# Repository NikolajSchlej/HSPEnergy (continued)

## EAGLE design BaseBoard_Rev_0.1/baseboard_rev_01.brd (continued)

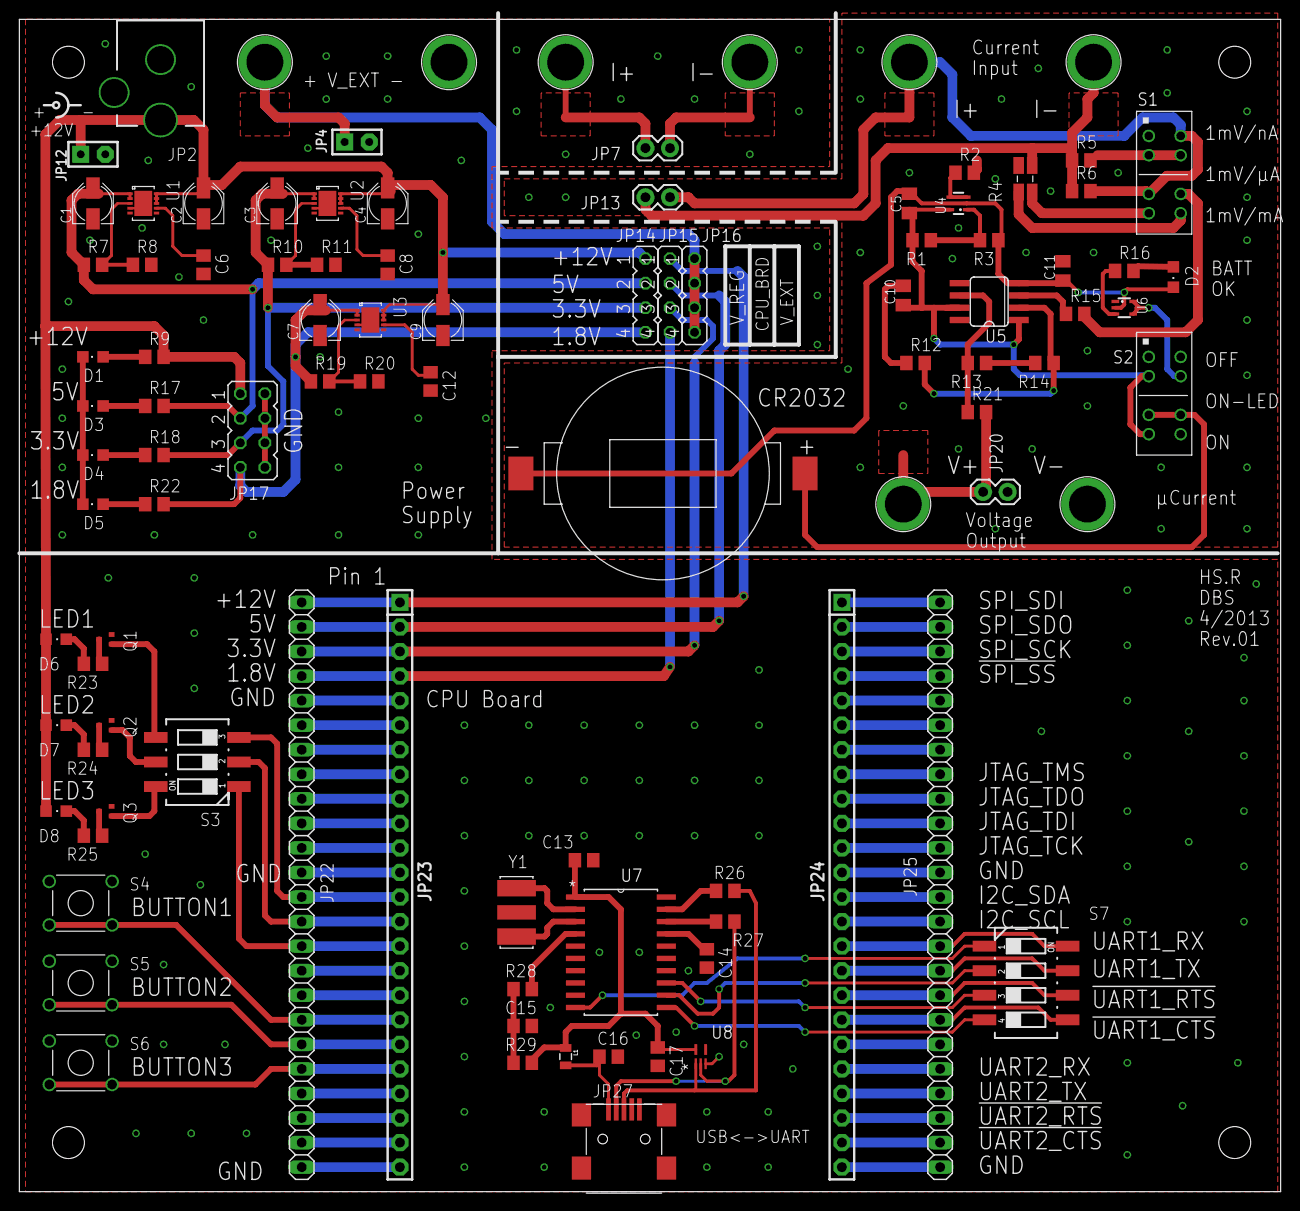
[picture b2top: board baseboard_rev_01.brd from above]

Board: 2 copper layers, 130.5 x 121.3 mm, 102 parts (0 on the bottom side), 105 nets.

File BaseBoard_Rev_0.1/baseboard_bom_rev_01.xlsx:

Designator | Quantity | Designator | Value1 | Value2 | Value3 | Package | Description | Manufacturer | Manufacturer # | Farnell # | Digikey # | Unit price € | Total Price €
Baseboard |  |  |  |  |  |  |  |  |  |  |  |  | 36.798999999999999
 | 3 | U1,U2,U3 | - |  |  | DFN10 | LDO voltage regulator |  | NCP3337MNADJR2G | 1901652 |  | 1.39 | 4.17
 | 6 | C1,C2,C3,C4,C7,C9 | 1uF |  |  | PANASONIC_B | Capacitor, polarized |  | EEE1HA010SR | 9697063 |  | 0.19900000000000001 | 1.194
 | 7 | C5,C10,C11,C13, C14, C15, C17 | 100nF |  |  | 0805 | Capacitor | Multicomp |  | 1759265 |  | 1.0999999999999999E-2 | 7.6999999999999999E-2
 | 4 | C6, C8, C12, C16 | 10nF |  |  | 0805 | Capacitor | Kemet |  | 1414662 |  | 2.1000000000000001E-2 | 8.4000000000000005E-2
 | 1 | JP2 | 1.95mm |  |  | - | DC connector | Multicomp |  | 1737246 |  | 0.64900000000000002 | 0.64900000000000002
 | 5 | R1,R3,R8,R11,R20 | 100k | 0.01 |  | 0805 | Resistor | WELWYN |  | 1099816 |  | 5.8000000000000003E-2 | 0.29000000000000004
 | 1 | S3 | 219-03 |  |  | - | DIP switch |  | MCEMR-03-T | 1524006 |  | 0.86699999999999999 | 0.86699999999999999
 | 1 | S7 | 219-04 |  |  | - | DIP switch |  | MCEMR-04-T | 1524007 |  | 0.94199999999999995 | 0.94199999999999995
 | 1 | L1 | 40 Ohm | 4A |  | 0805 | Inductor |  |  | 2292459 |  | 4.2999999999999997E-2 | 4.2999999999999997E-2
 | 3 | Q1, Q2, Q3 | PDTC114E |  |  | SOT416 | SMT resistor-equipped transistor | NXP | PDTC114EE | 1757984 | - | 1.7999999999999999E-2 | 5.3999999999999992E-2
 | 1 | R10 | 165k | 0.01 |  | 0805 | Resistor | Vishay |  | 2139046 |  | 8.0000000000000002E-3 | 8.0000000000000002E-3
 | 2 | R16, R28 | 470R | 0.01 |  | 0805 | Resistor |  |  | 1099798 |  | 1.4999999999999999E-2 | 0.03
 | 1 | R19 | 44k | 0.01 |  | 0805 | Resistor |  |  | 2141459 |  | 2.5999999999999999E-2 | 2.5999999999999999E-2
 | 3 | R2, R15, R21 | 100R | 0.01 |  | 0805 | Resistor |  |  | 1887253 |  | 6.2E-2 | 0.186
 | 2 | R26, R27 | 27R | 0.01 |  | 0805 | Resistor |  |  | 1500696 |  | 4.8000000000000001E-2 | 9.6000000000000002E-2
 | 1 | R29 | 10k | 0.01 |  | 0805 | Resistor |  |  | 1612522 |  | 3.2000000000000001E-2 | 3.2000000000000001E-2
 | 1 | R5 | 10R | 0.1% |  | 0805 | Resistor |  |  | 2008313 |  | 0.189 | 0.189
 | 1 | R6 | 10K | 0.1% |  | 0805 | Resistor |  |  | 1653282 |  | 0.10199999999999999 | 0.10199999999999999
 | 1 | R12 | 1K | 0.1% |  | 0805 | Resistor |  |  | 1653252 |  | 0.10199999999999999 | 0.10199999999999999
 | 1 | R13 | 24K | 0.1% |  | 0805 | Resistor |  |  | 1506115 |  | 0.20399999999999999 | 0.20399999999999999
 | 1 | R14 | 75K | 0.1% |  | 0805 | Resistor |  |  | 1653312 |  | 0.10199999999999999 | 0.10199999999999999
 | 1 | R7 | 300k | 0.01 |  | 0805 | Resistor |  |  | 1400387 |  | 2.3E-2 | 2.3E-2
 | 4 | R9,R23, R24, R25 | 5k6 | 0.01 |  | 0805 | Resistor, LED, 12V |  |  | 1500725 |  | 4.2000000000000003E-2 | 0.16800000000000001
 | 1 | R17 | 2k2 | 0.01 |  | 0805 | Resistor, LED, 5V |  |  | 1500692 |  | 0.252 | 0.252
 | 1 | R18 | 820R | 0.01 |  | 0805 | Resistor, LED, 3.3V |  |  | 1100314 |  | 2.1999999999999999E-2 | 2.1999999999999999E-2
 | 1 | R22 | 56R | 0.01 |  | 0805 | Resistor, LED, 1.8V |  |  | 1500723 |  | 7.8E-2 | 7.8E-2
 | 3 | S4, S5, S6 | - |  |  | - | Switch SPST-NO | ALPS | SKHHBWA010 | 2056816 |  | 0.16200000000000001 | 0.64800000000000002
 | 4 | D1, D3, D4, D5 | 1.8V | 2mA |  | 0805 | LED red | ROHM |  | 1685056 |  | 0.626 | 2.504
 | 4 | D2, D6, D7, D8 | 1.8V | 2mA |  | 0805 | LED orange | ROHM |  | 1685055 |  | 0.626 | 2.504
 | 2 | JP22, JP25 | 1x24 |  |  | - | pin header male |  |  | 1593425 |  | 0.67100000000000004 | 1.3420000000000001
 | 2 | JP23, JP24 | 1x24 |  |  | - | pin header female |  |  | 1593472 |  | 0.91800000000000004 | 1.8360000000000001
 | 5 | JP4, JP12,JP7, JP13, JP20 | 1x02 |  |  | - | pin header male |  |  | 1022245 |  | 0.113 | 0.56500000000000006
 | 1 | JP17 | 2x04 |  |  | - | pin header male |  |  | 1022233 |  | 0.47699999999999998 | 0.47699999999999998
 | 3 | JP14, JP15, JP16 | 1x04 |  |  | - | pin header male |  |  | 1022251 |  | 0.22900000000000001 | 0.68700000000000006
 | 4 | JP3, JP6, JP9, JP19 | - |  |  | - | 4mm Banana conector, red |  |  | 1698950 |  | 0.874 | 3.496
 | 4 | JP5,JP8,JP10,JP21 | - |  |  | - | 4mm Banana conector, black |  |  | 1698951 |  | 0.874 | 3.496
uCurrent
 | 1 | U4 |  |  |  | SC70-5L | uCurrent: op amp |  | LMV321IDCKR | 1651880 |  | 0.317 | 0.317
 | 1 | U6 |  |  |  | DCK | uCurrent: voltage supervisor | Texas Instruments | TPS3801L30DCKR | 2075439 |  | 1.03 | 1.03
 | 1 | U5 |  |  |  | 8 SO | uCurrent: op amp | Maxim | MAX4239ASA+ | - | MAX4239ASA+-ND | 2.02 | 2.02
 | 1 | R4 | 0R01 | 5.0000000000000001E-3 |  | 1206 | KELVIN R01 | Ohmite | LVK12R010DER | 1462291 |  | 0.58099999999999996 | 0.58099999999999996
 | 2 | S1,S2 | DP3T |  |  | custom | slide switch | C&K Components | JS203011CQN | - | 401-2004-ND | 0.46 | 0.92
 | 1 | JP18 |  |  |  | custom | CR2032 Battery holder | Renata | SMTU 2032-LF | 1216354 |  | 0.85499999999999998 | 0.85499999999999998
 | 1 |  |  |  |  | - | CR2032 Battery
USB-to-serial
 | 1 | U8 |  |  |  | SOT-5 | USB ESD protection array | Texas Instruments | TPD3E001DRLR | 1603422 |  | 0.21 | 0.21
 | 1 | U7 |  |  |  | SOIC | USB-to-serial converter | Microchip | MCP2200-I/SO | 1781148 |  | 1.81 | 1.81
 | 1 | Y1 |  |  | 12MHz | custom | Quarz oscillator |  | PBRC12.00HR50X0RZ | 1218535 |  | 0.75900000000000001 | 0.75900000000000001
 | 1 | JP27 | - | - | - |  | mini USB B, female |  | 10033526-N3212MLF | 2112367 |  | 0.752 | 0.752

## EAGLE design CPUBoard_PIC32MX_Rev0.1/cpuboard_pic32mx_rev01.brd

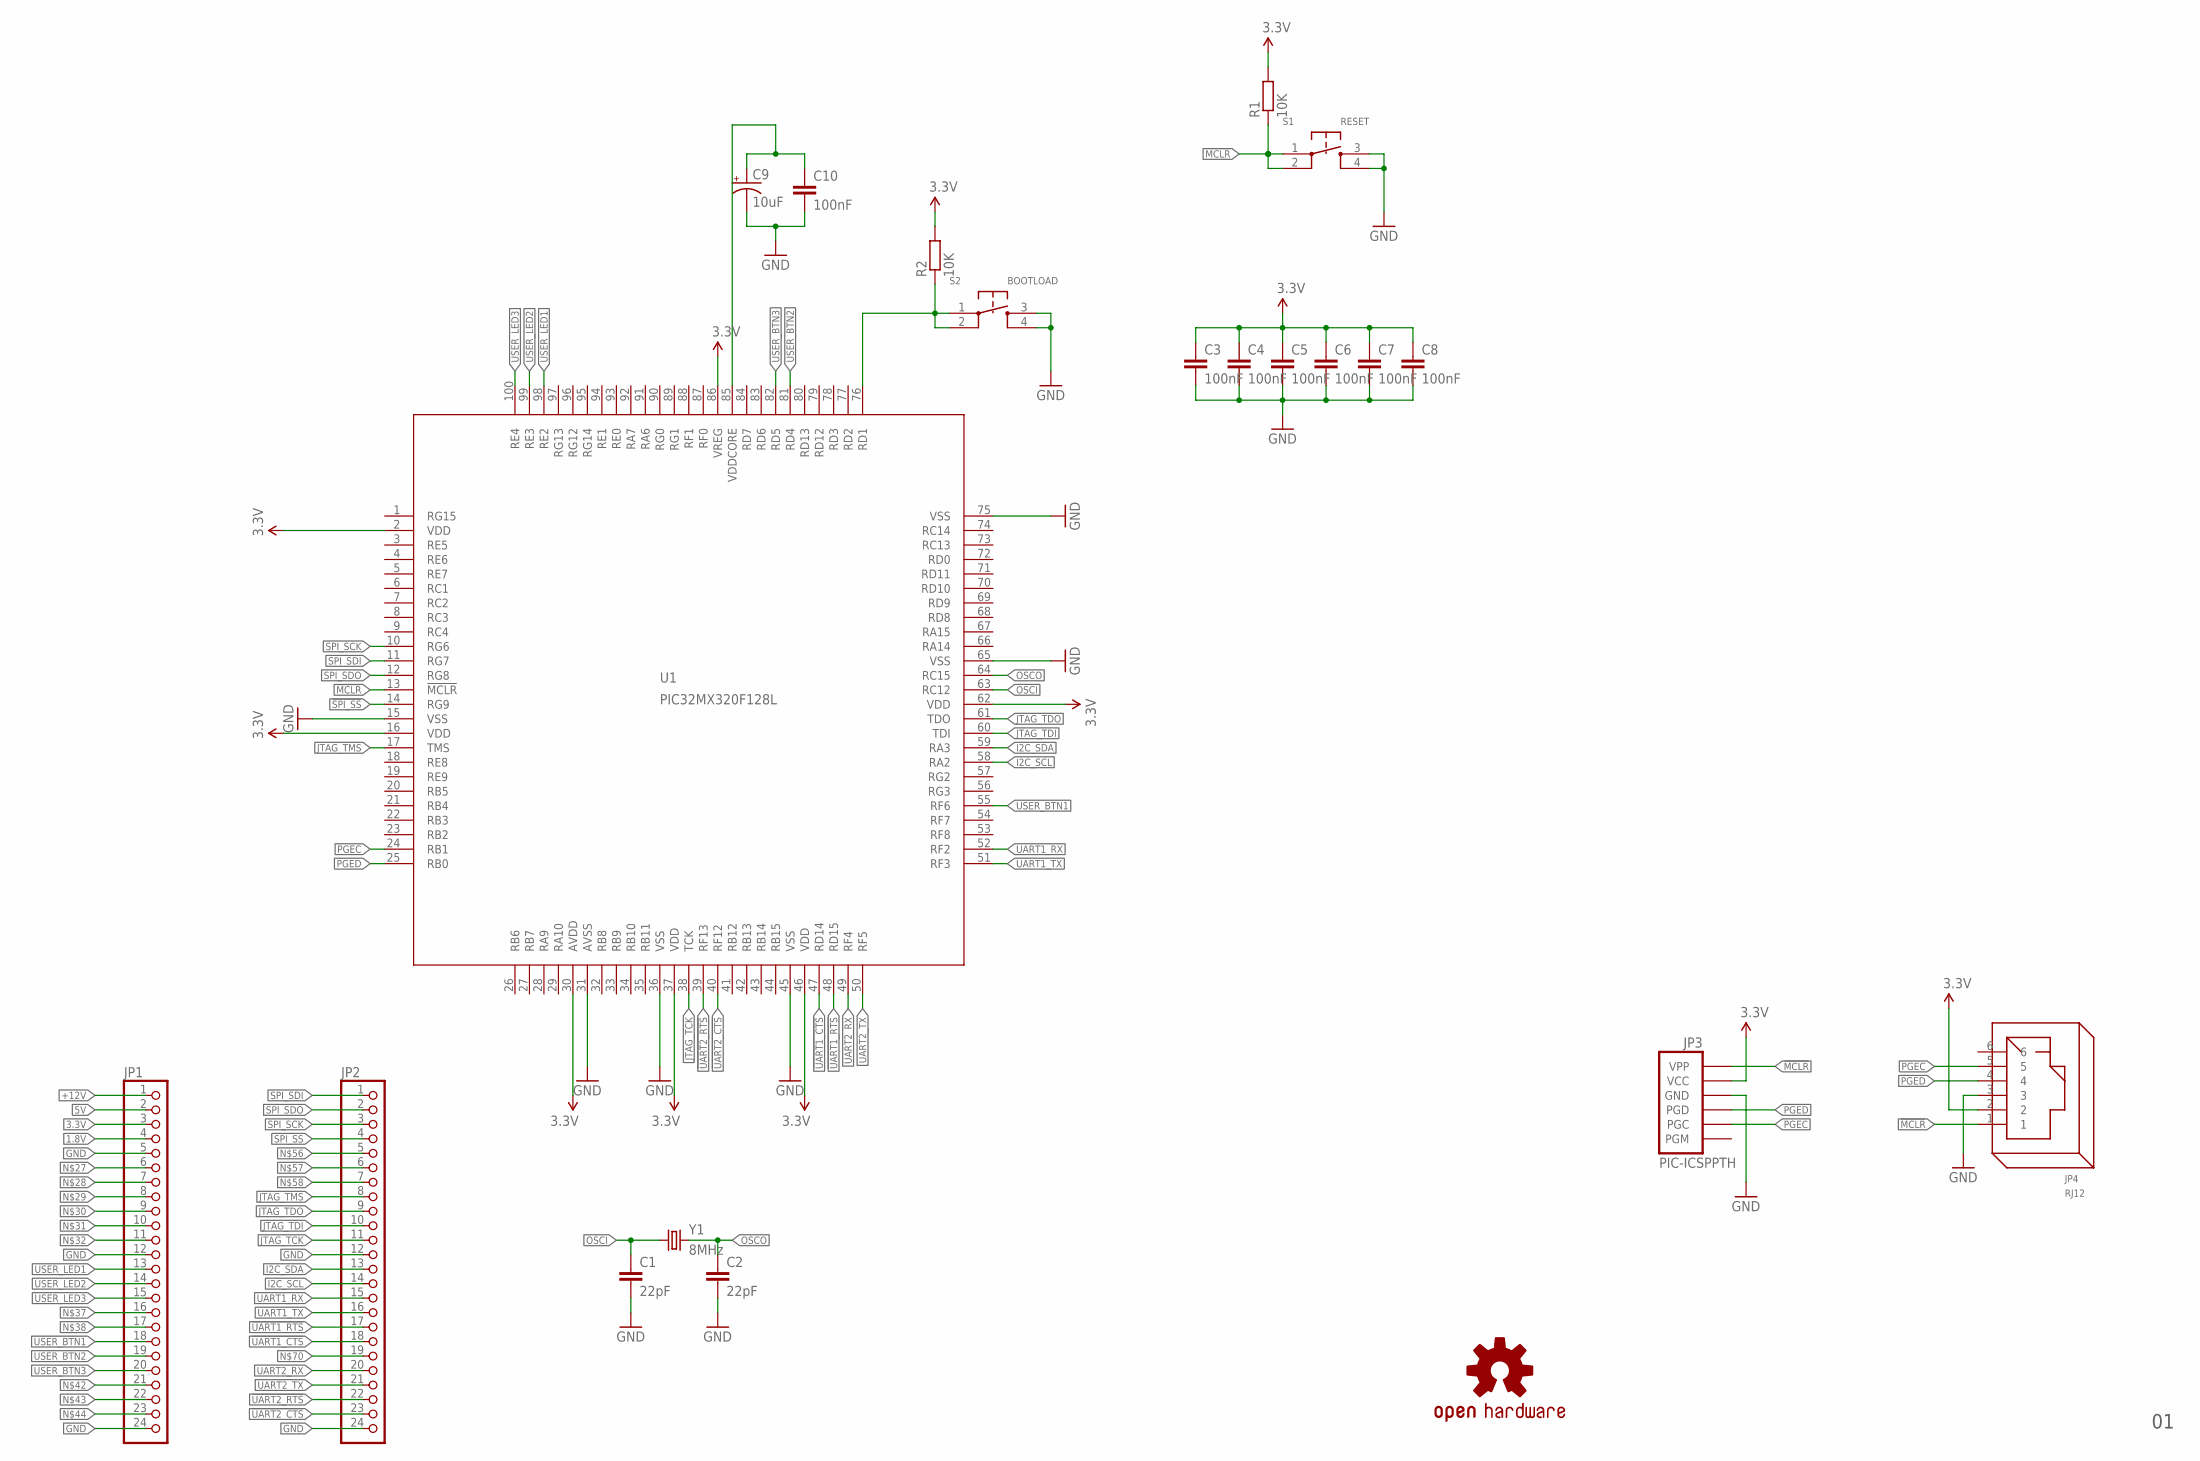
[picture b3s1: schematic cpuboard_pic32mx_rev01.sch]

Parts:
C1, C2: 22pF; C0805K
C3, C4, C5, C6, C7, C8, C10: 100nF; C0805K
C9: 10uF; PANASONIC_D
JP1, JP2: PINHD-1X24; 1X24
JP3: PIC-ICSPPTH; MOLEX-1X6
JP4: RJ12
R1, R2: 10K; R0805
S1: RESET; SWITCH_TROUGHHOLE
S2: BOOTLOAD; SWITCH_TROUGHHOLE
U1: PIC32MX320F128L; SQFP-S-12X12-100
U$1: OSHW-LOGOS; OSHW-LOGO-S
Y1: 8MHz; HC49UP

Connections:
1.8V: JP1.4
3.3V: C3.1, C4.1, C5.1, C6.1, C7.1, C8.1, JP1.3, JP3.5 (VCC), JP4.2, R1.2, R2.2, U1.2 (VDD), U1.16 (VDD), U1.30 (AVDD), U1.37 (VDD), U1.46 (VDD), U1.62 (VDD), U1.86 (VREG)
5V: JP1.2
!MCLR: JP3.6 (VPP), JP4.1, R1.1, S1.1, S1.2, U1.13 (!MCLR)
!SPI_SS: JP2.4, U1.14 (RG9)
!UART1_CTS: JP2.18, U1.47 (RD14)
!UART1_RTS: JP2.17, U1.48 (RD15)
!UART2_CTS: JP2.23, U1.40 (RF12)
!UART2_RTS: JP2.22, U1.39 (RF13)
+12V: JP1.1
GND: C1.2, C2.2, C3.2, C4.2, C5.2, C6.2, C7.2, C8.2, C9.-, C10.2, JP1.5, JP1.12, JP1.24, JP2.12, JP2.24, JP3.4 (GND), JP4.3, S1.3, S1.4, S2.3, S2.4, U1.15 (VSS), U1.31 (AVSS), U1.36 (VSS), U1.45 (VSS), U1.65 (VSS), U1.75 (VSS)
I2C_SCL: JP2.14, U1.58 (RA2)
I2C_SDA: JP2.13, U1.59 (RA3)
JTAG_TCK: JP2.11, U1.38 (TCK)
JTAG_TDI: JP2.10, U1.60 (TDI)
JTAG_TDO: JP2.9, U1.61 (TDO)
JTAG_TMS: JP2.8, U1.17 (TMS)
unnamed: C9.+, C10.1, U1.85 (VDDCORE)
unnamed: R2.1, S2.1, S2.2, U1.76 (RD1)
OSCI: C1.1, U1.63 (RC12), Y1.1
OSCO: C2.1, U1.64 (RC15), Y1.2
PGEC: JP3.2 (PGC), JP4.5, U1.24 (RB1)
PGED: JP3.3 (PGD), JP4.4, U1.25 (RB0)
SPI_SCK: JP2.3, U1.10 (RG6)
SPI_SDI: JP2.1, U1.11 (RG7)
SPI_SDO: JP2.2, U1.12 (RG8)
UART1_RX: JP2.15, U1.52 (RF2)
UART1_TX: JP2.16, U1.51 (RF3)
UART2_RX: JP2.20, U1.49 (RF4)
UART2_TX: JP2.21, U1.50 (RF5)
USER_BTN1: JP1.18, U1.55 (RF6)
USER_BTN2: JP1.19, U1.81 (RD4)
USER_BTN3: JP1.20, U1.82 (RD5)
USER_LED1: JP1.13, U1.98 (RE2)
USER_LED2: JP1.14, U1.99 (RE3)
USER_LED3: JP1.15, U1.100 (RE4)

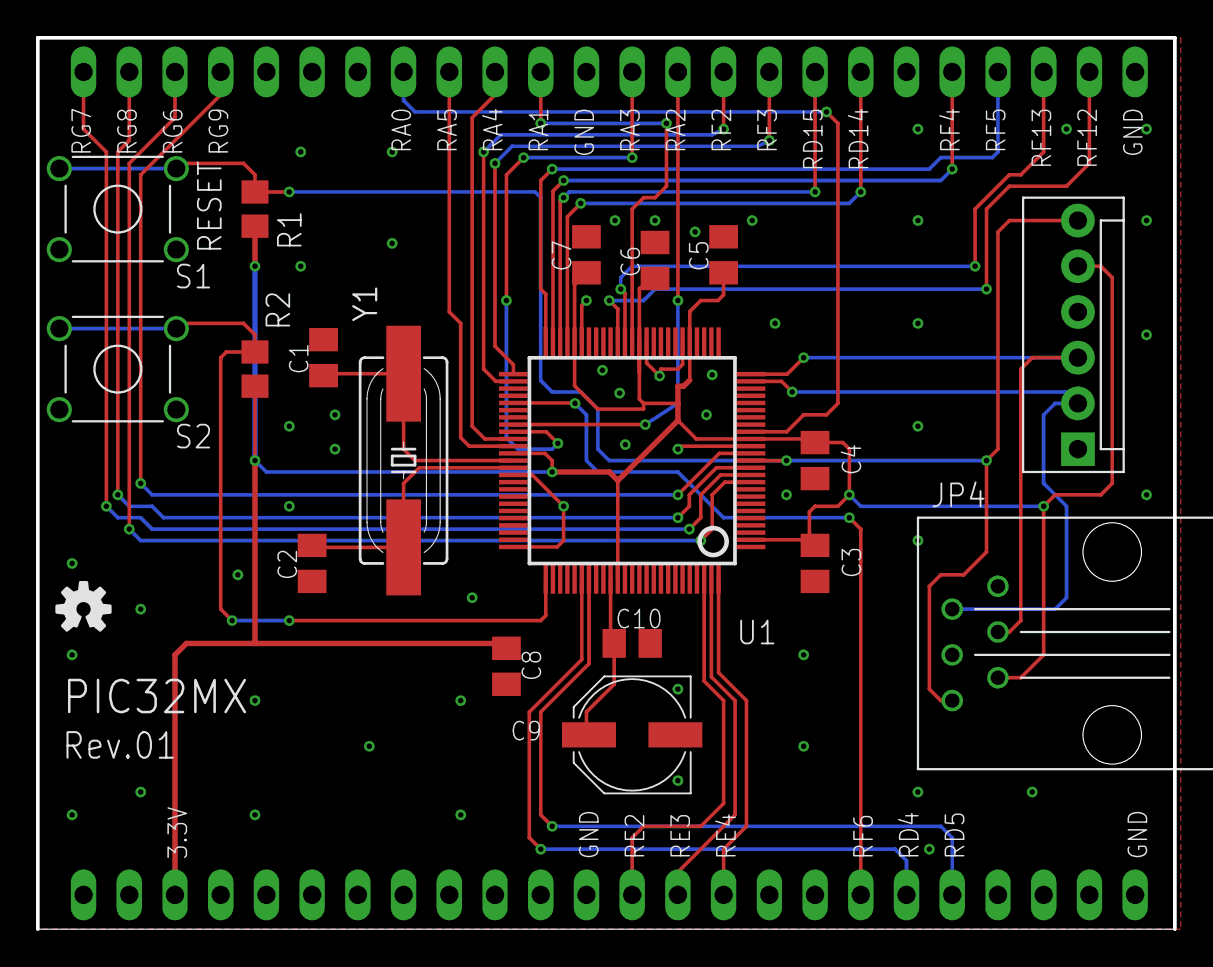
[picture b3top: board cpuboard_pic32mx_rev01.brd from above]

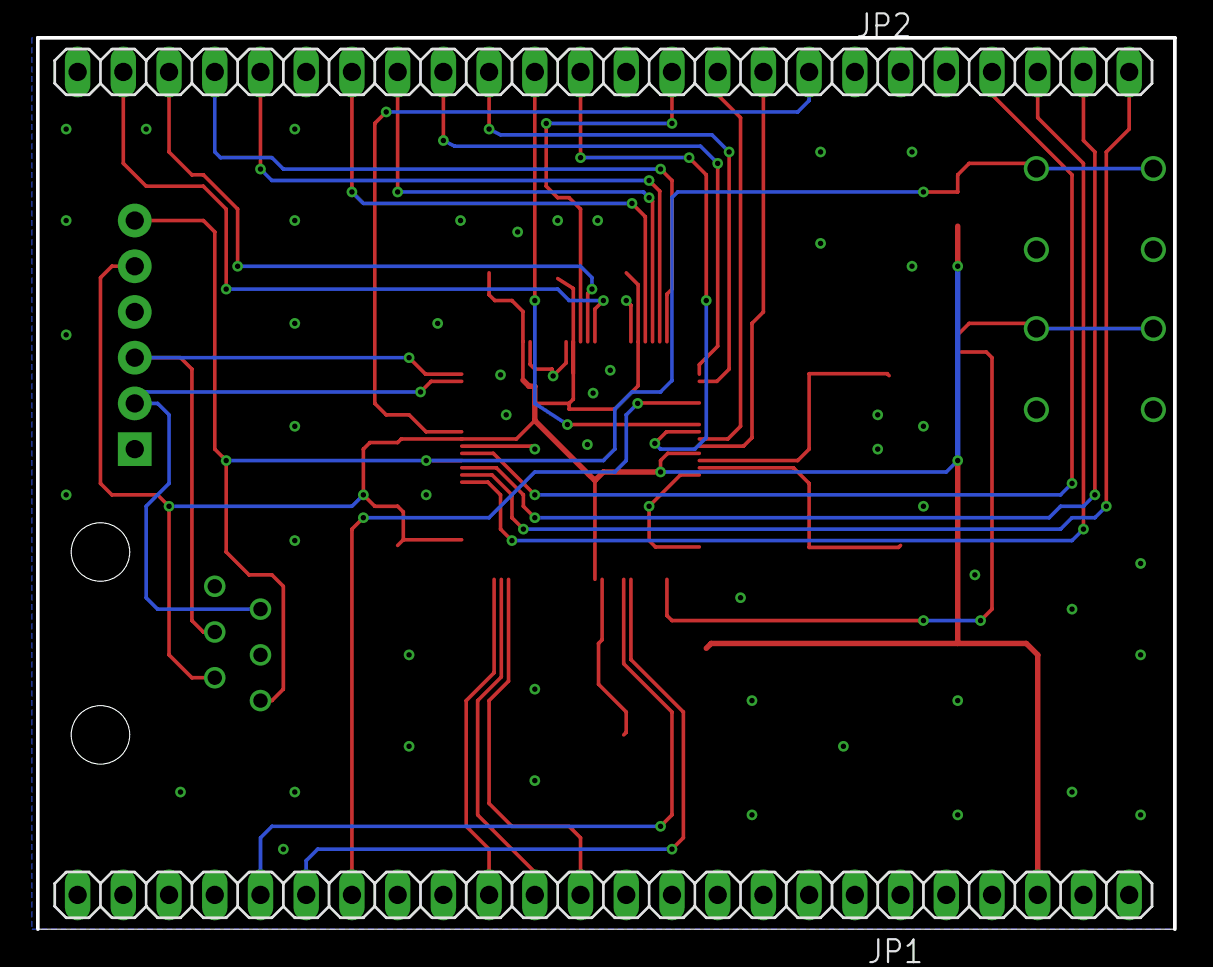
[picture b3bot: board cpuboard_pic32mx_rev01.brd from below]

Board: 2 copper layers, 63.2 x 49.5 mm, 21 parts (2 on the bottom side), 33 nets.

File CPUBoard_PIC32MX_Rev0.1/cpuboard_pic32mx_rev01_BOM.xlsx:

Designator | Quantity | Designator | Value1 | Value2 | Value3 | Package | Description | Manufacturer | Manufacturer # | Farnell # | Digikey # | Unit price € | Total Price €
 | 1 |  |  |  |  | TQFP-100 | Microcontroller | Microchip | PIC32MX320F128L | 1523321 | PIC32MX320F128L-80I/PT | 6.67 | 6.67
 | 1 | C9 | 10uF | 50V | +/- 20% | SMT | Aluminum Electrolytic Capacitor | Panasonic | EEEFK1H100P | 1850117 |  | 0.26900000000000002 | 0.26900000000000002
 | 2 |  | 1x24 |  |  |  | pin header male |  |  | 1593425 |  | 0.67100000000000004 | 1.3420000000000001
 | 2 | C1,C2 | 22pF |  |  | 0805 | Capacitor |  |  | 1885437 |  | 0.29699999999999999 | 0.59399999999999997
 | 7 | C3,C4,C5,C6,C7,C8,C10 | 100nF |  |  | 0805 | Capacitor | Multicomp |  | 1759265 |  | 1.0999999999999999E-2 | 7.6999999999999999E-2
DNP | 1 | JP3 |  |  |  |  | Programming connector
 | 1 | JP4 | RJ12 |  |  |  | Programming connector |  |  | 3938359 |  | 1.18 | 1.18
 | 2 | R1,R2 | 10K | 1% |  | 0805 | Resistor |  |  | 1612522 |  | 3.2000000000000001E-2 | 6.4000000000000001E-2
 | 2 | S1,S2 |  |  |  |  | tactile switch | ALPS | SKHHBWA010 | 2056816 |  | 0.16200000000000001 | 0.16200000000000001

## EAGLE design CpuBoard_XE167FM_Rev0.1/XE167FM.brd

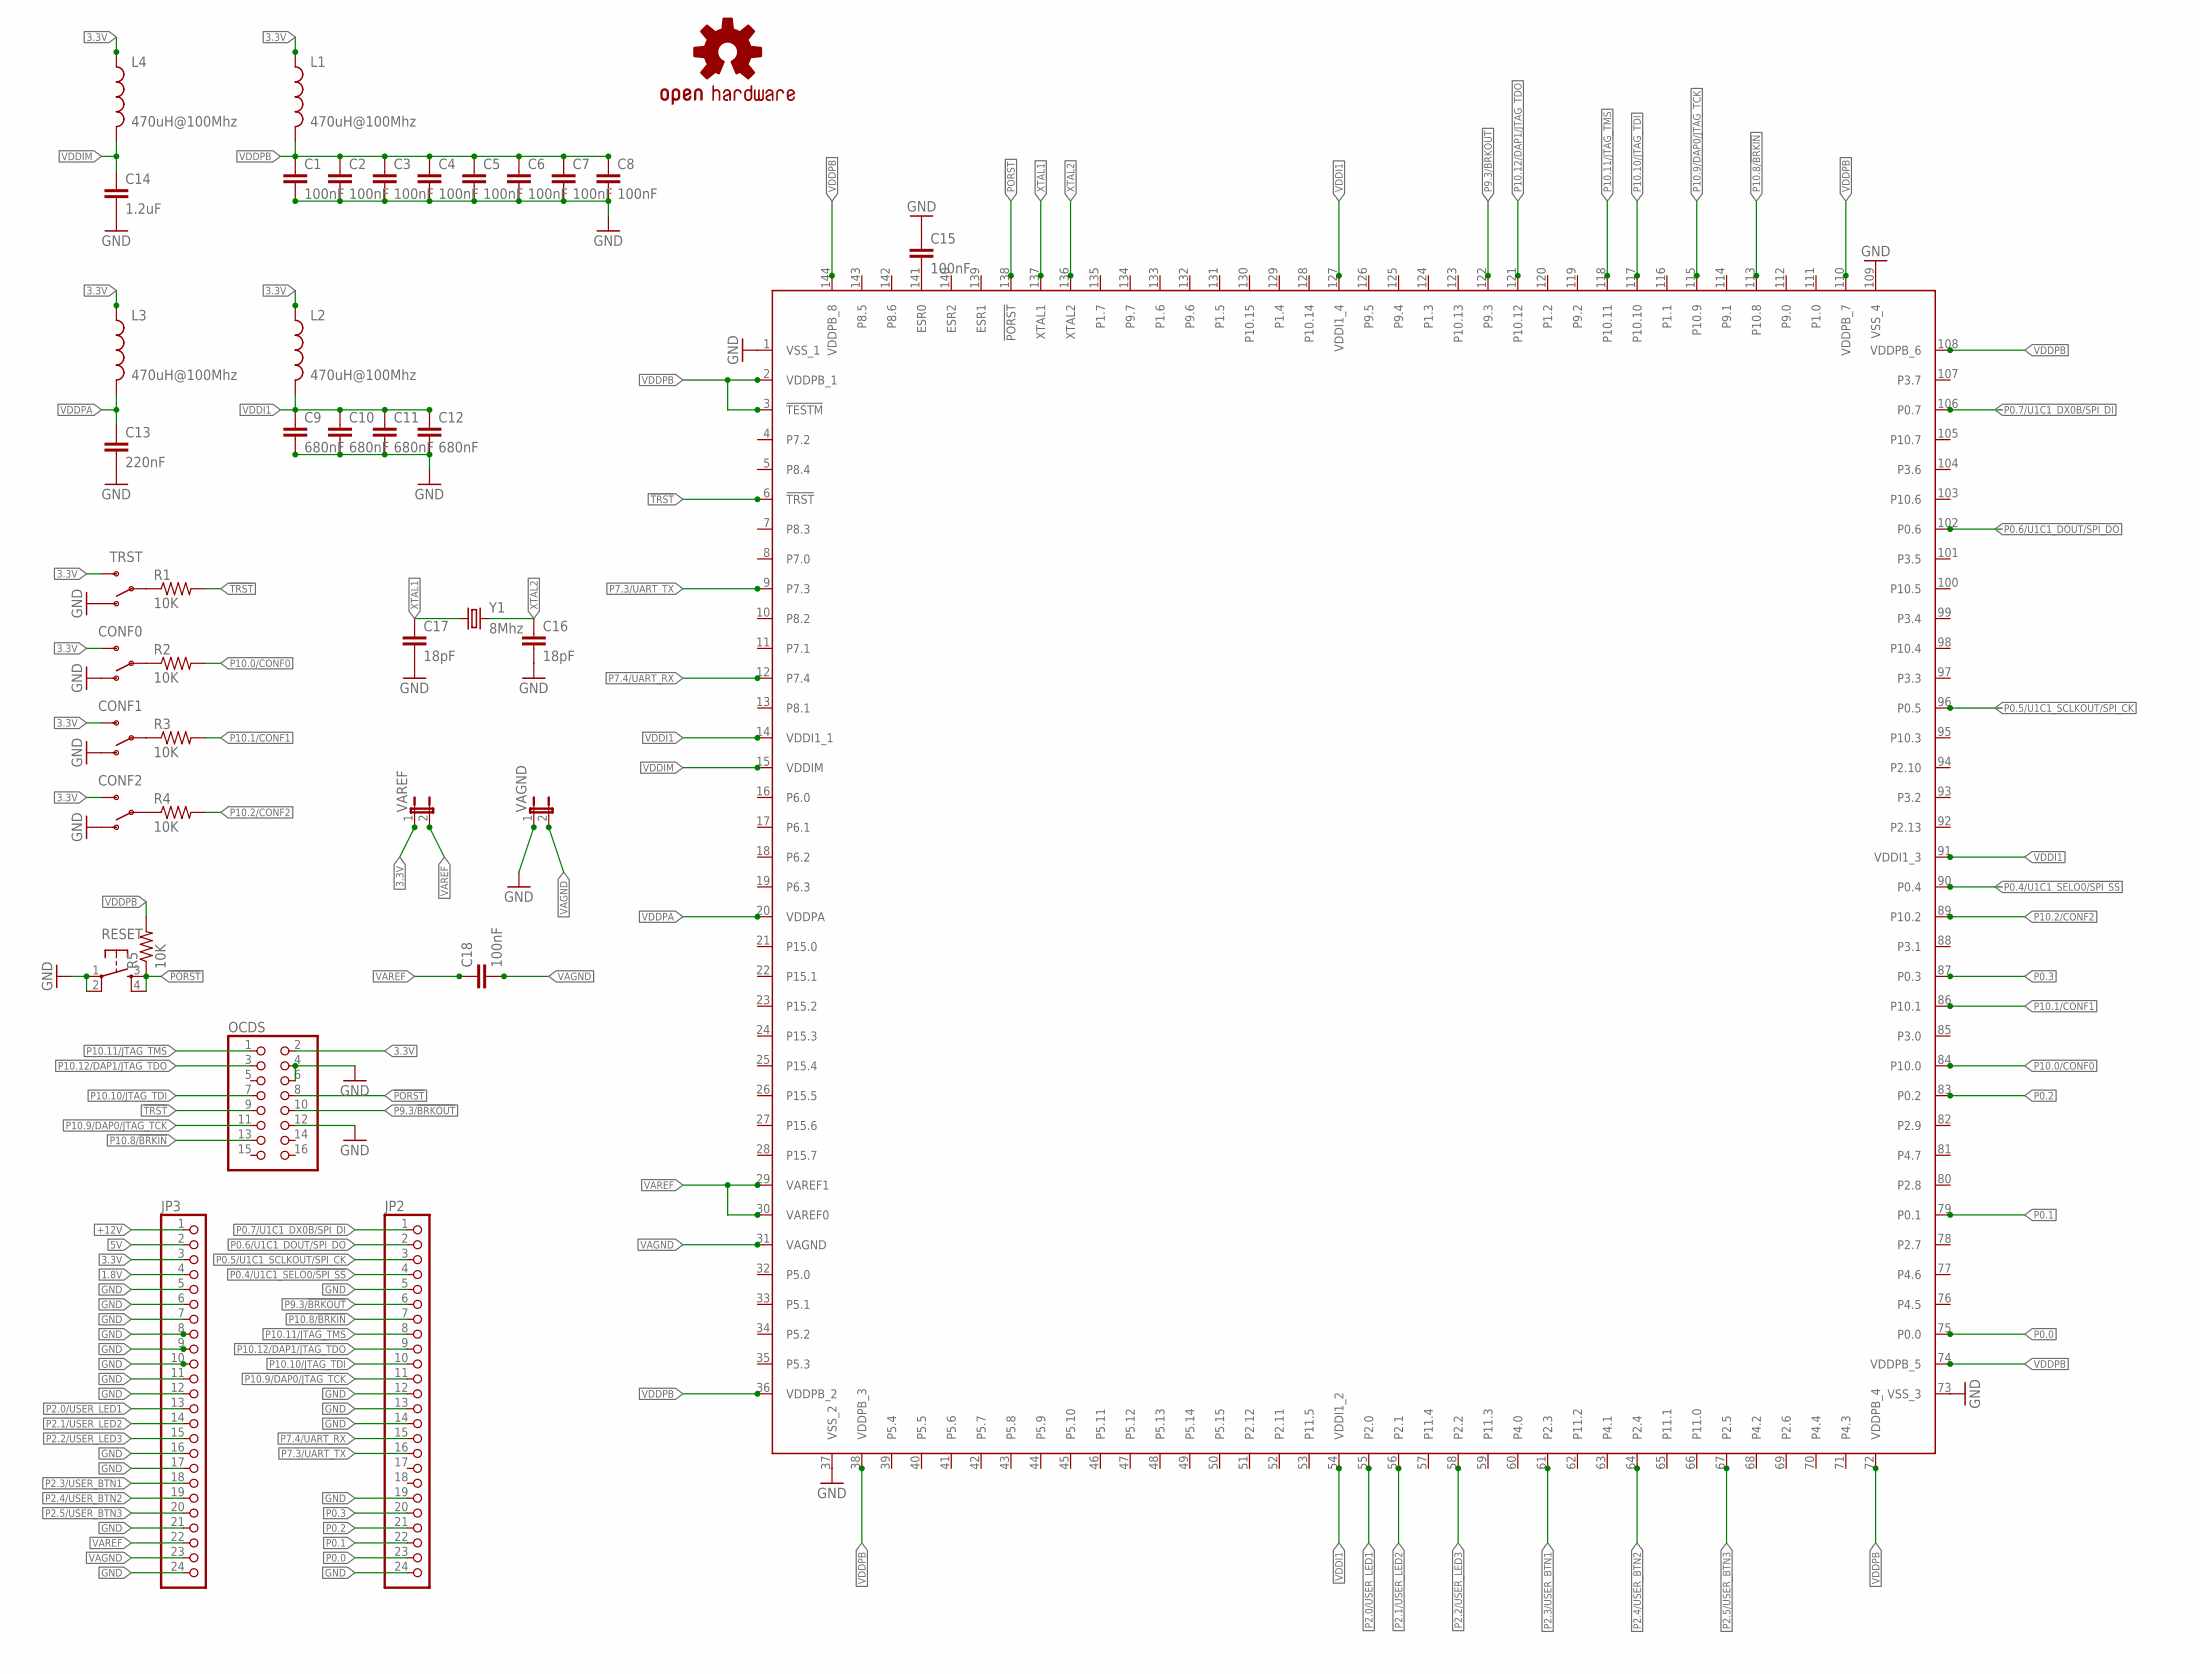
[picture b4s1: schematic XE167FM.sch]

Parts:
C1, C2, C3, C4, C5, C6, C7, C8, C15, C18: 100nF; 0603-CAP
C9, C10, C11, C12: 680nF; 0603-CAP
C13: 220nF; 0603-CAP
C14: 1.2uF; 0603-CAP
C16, C17: 18pF; 0603-CAP
CONF0, CONF1, CONF2: SWITCH-SPDTPTH; SWITCH-SPDT
IC1: XE167FM; LQFP144
JP2, JP3: PINHD-1X24; 1X24
L1, L2, L3, L4: 470uH@100Mhz; 0603
LOGO1: OSHW-LOGOS; OSHW-LOGO-S
OCDS: PINHD-2X8_2.54; 2X08
R1, R2, R3, R4, R5: 10K; 0603-RES
RESET: TAC_SWITCHPTH; TACTILE-PTH
TRST: SWITCH-SPDTPTH; SWITCH-SPDT
VAGND: JP1E; JP1
VAREF: JP1E; JP1
Y1: 8Mhz; HC49UP

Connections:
1.8V: JP3.4
3.3V: CONF0.3 (S), CONF1.3 (S), CONF2.3 (S), JP3.3, L1.1, L2.1, L3.1, L4.1, OCDS.2, TRST.3 (S), VAREF.1
5V: JP3.2
!PORST: IC1.138 (!PORST), OCDS.8, R5.1, RESET.3, RESET.4
!TRST: IC1.6 (!TRST), OCDS.9, R1.2
+12V: JP3.1
GND: C1.2, C2.2, C3.2, C4.2, C5.2, C6.2, C7.2, C8.2, C9.2, C10.2, C11.2, C12.2, C13.2, C14.2, C15.1, C16.2, C17.2, CONF0.1 (O), CONF1.1 (O), CONF2.1 (O), IC1.1 (VSS_1), IC1.37 (VSS_2), IC1.73 (VSS_3), IC1.109 (VSS_4), JP2.5, JP2.12, JP2.13, JP2.14, JP2.19, JP2.24, JP3.5, JP3.6, JP3.7, JP3.8, JP3.9, JP3.10, JP3.11, JP3.12, JP3.16, JP3.17, JP3.21, JP3.24, OCDS.4, OCDS.6, OCDS.12, RESET.1, RESET.2, TRST.1 (O), VAGND.1
unnamed: R1.1, TRST.2
unnamed: CONF0.2, R2.1
unnamed: CONF1.2, R3.1
unnamed: CONF2.2, R4.1
unnamed: C15.2, IC1.141 (ESR0)
P0.0: IC1.75 (P0.0), JP2.23
P0.1: IC1.79 (P0.1), JP2.22
P0.2: IC1.83 (P0.2), JP2.21
P0.3: IC1.87 (P0.3), JP2.20
P0.4/U1C1_SELO0/!SPI_SS: IC1.90 (P0.4), JP2.4
P0.5/U1C1_SCLKOUT/SPI_CK: IC1.96 (P0.5), JP2.3
P0.6/U1C1_DOUT/SPI_DO: IC1.102 (P0.6), JP2.2
P0.7/U1C1_DX0B/SPI_DI: IC1.106 (P0.7), JP2.1
P2.0/USER_LED1: IC1.55 (P2.0), JP3.13
P2.1/USER_LED2: IC1.56 (P2.1), JP3.14
P2.2/USER_LED3: IC1.58 (P2.2), JP3.15
P2.3/USER_BTN1: IC1.61 (P2.3), JP3.18
P2.4/USER_BTN2: IC1.64 (P2.4), JP3.19
P2.5/USER_BTN3: IC1.67 (P2.5), JP3.20
P7.3/UART_TX: IC1.9 (P7.3), JP2.16
P7.4/UART_RX: IC1.12 (P7.4), JP2.15
P9.3/!BRKOUT: IC1.122 (P9.3), JP2.6, OCDS.10
P10.0/CONF0: IC1.84 (P10.0), R2.2
P10.1/CONF1: IC1.86 (P10.1), R3.2
P10.2/CONF2: IC1.89 (P10.2), R4.2
P10.8/!BRKIN: IC1.113 (P10.8), JP2.7, OCDS.13
P10.9/DAP0/JTAG_TCK: IC1.115 (P10.9), JP2.11, OCDS.11
P10.10/JTAG_TDI: IC1.117 (P10.10), JP2.10, OCDS.7
P10.11/JTAG_TMS: IC1.118 (P10.11), JP2.8, OCDS.1
P10.12/DAP1/JTAG_TDO: IC1.121 (P10.12), JP2.9, OCDS.3
VAGND: C18.2, IC1.31 (VAGND), JP3.23, VAGND.2
VAREF: C18.1, IC1.29 (VAREF1), IC1.30 (VAREF0), JP3.22, VAREF.2
VDDI1: C9.1, C10.1, C11.1, C12.1, IC1.14 (VDDI1_1), IC1.54 (VDDI1_2), IC1.91 (VDDI1_3), IC1.127 (VDDI1_4), L2.2
VDDIM: C14.1, IC1.15 (VDDIM), L4.2
VDDPA: C13.1, IC1.20 (VDDPA), L3.2
VDDPB: C1.1, C2.1, C3.1, C4.1, C5.1, C6.1, C7.1, C8.1, IC1.2 (VDDPB_1), IC1.3 (!TESTM), IC1.36 (VDDPB_2), IC1.38 (VDDPB_3), IC1.72 (VDDPB_4), IC1.74 (VDDPB_5), IC1.108 (VDDPB_6), IC1.110 (VDDPB_7), IC1.144 (VDDPB_8), L1.2, R5.2
XTAL1: C17.1, IC1.137 (XTAL1), Y1.1
XTAL2: C16.1, IC1.136 (XTAL2), Y1.2

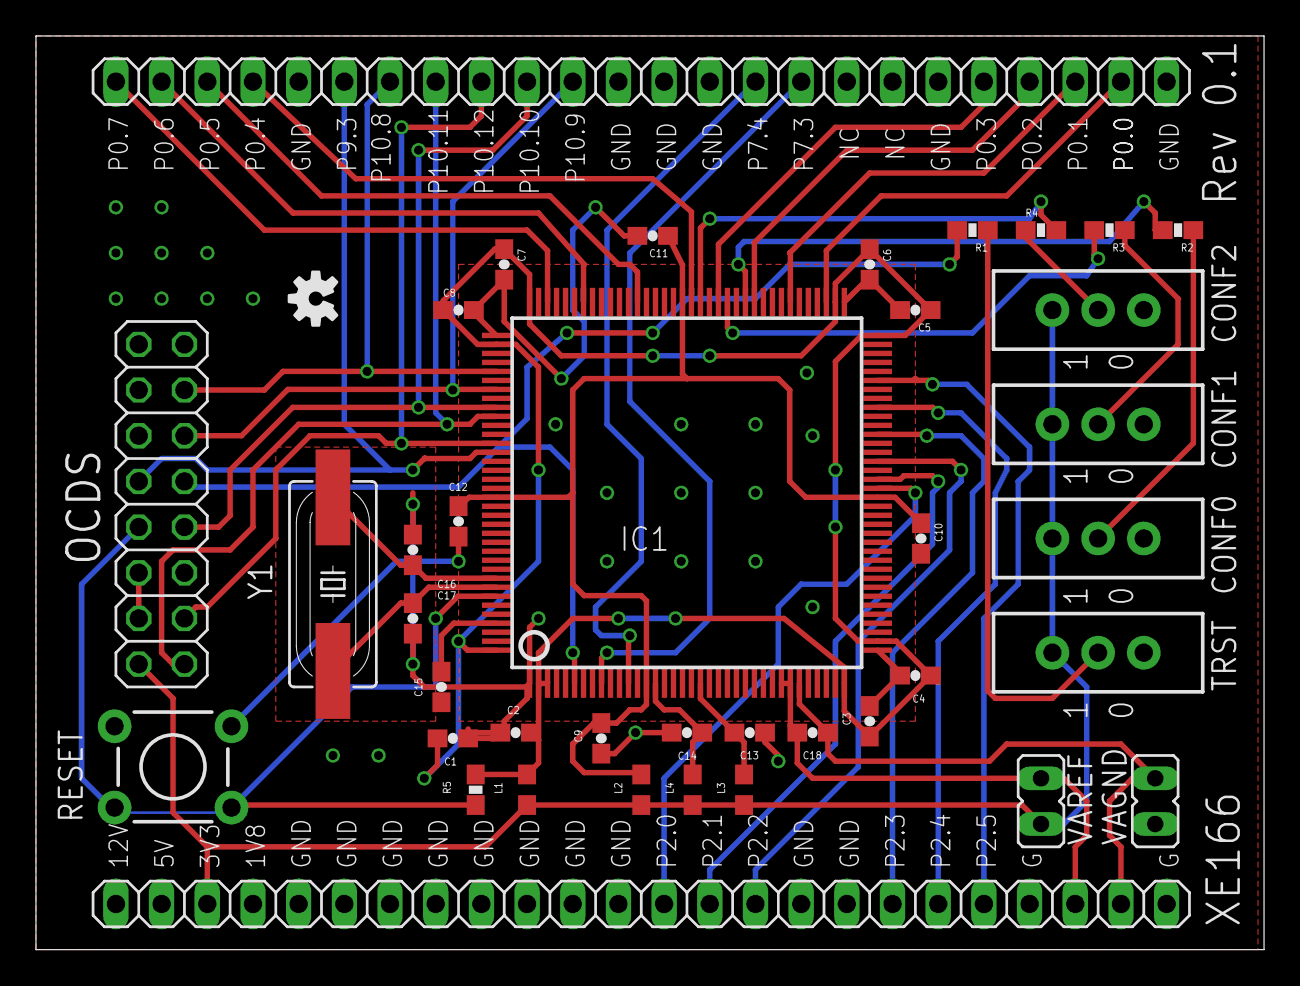
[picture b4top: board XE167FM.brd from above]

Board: 2 copper layers, 68.3 x 50.8 mm, 40 parts (0 on the bottom side), 42 nets.

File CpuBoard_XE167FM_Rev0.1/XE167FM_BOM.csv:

"Part";"Value";"Device";"Package";"Description";"";
"C1";"100nF";"CAP0603-CAP";"0603-CAP";"Capacitor";"";
"C2";"100nF";"CAP0603-CAP";"0603-CAP";"Capacitor";"";
"C3";"100nF";"CAP0603-CAP";"0603-CAP";"Capacitor";"";
"C4";"100nF";"CAP0603-CAP";"0603-CAP";"Capacitor";"";
"C5";"100nF";"CAP0603-CAP";"0603-CAP";"Capacitor";"";
"C6";"100nF";"CAP0603-CAP";"0603-CAP";"Capacitor";"";
"C7";"100nF";"CAP0603-CAP";"0603-CAP";"Capacitor";"";
"C8";"100nF";"CAP0603-CAP";"0603-CAP";"Capacitor";"";
"C9";"680nF";"CAP0603-CAP";"0603-CAP";"Capacitor";"";
"C10";"680nF";"CAP0603-CAP";"0603-CAP";"Capacitor";"";
"C11";"680nF";"CAP0603-CAP";"0603-CAP";"Capacitor";"";
"C12";"680nF";"CAP0603-CAP";"0603-CAP";"Capacitor";"";
"C13";"220nF";"CAP0603-CAP";"0603-CAP";"Capacitor";"";
"C14";"1.2uF";"CAP0603-CAP";"0603-CAP";"Capacitor";"";
"C15";"100nF";"CAP0603-CAP";"0603-CAP";"Capacitor";"";
"C16";"18pF";"CAP0603-CAP";"0603-CAP";"Capacitor";"";
"C17";"18pF";"CAP0603-CAP";"0603-CAP";"Capacitor";"";
"C18";"100nF";"CAP0603-CAP";"0603-CAP";"Capacitor";"";
"CONF0";"";"SWITCH-SPDTPTH";"SWITCH-SPDT";"SPDT Switch";"";
"CONF1";"";"SWITCH-SPDTPTH";"SWITCH-SPDT";"SPDT Switch";"";
"CONF2";"";"SWITCH-SPDTPTH";"SWITCH-SPDT";"SPDT Switch";"";
"IC1";"XE167FM";"XE167FM";"LQFP144";"Infineon XE167FM";"";
"JP2";"";"PINHD-1X24";"1X24";"PIN HEADER";"";
"JP3";"";"PINHD-1X24";"1X24";"PIN HEADER";"";
"L1";"470uH@100Mhz";"INDUCTOR0603";"0603";"Inductors";"";
"L2";"470uH@100Mhz";"INDUCTOR0603";"0603";"Inductors";"";
"L3";"470uH@100Mhz";"INDUCTOR0603";"0603";"Inductors";"";
"L4";"470uH@100Mhz";"INDUCTOR0603";"0603";"Inductors";"";
"OCDS";"";"PINHD-2X8_2.54";"2X08";"PIN HEADER";"";
"R1";"10K";"RESISTOR0603-RES";"0603-RES";"Resistor";"";
"R2";"10K";"RESISTOR0603-RES";"0603-RES";"Resistor";"";
"R3";"10K";"RESISTOR0603-RES";"0603-RES";"Resistor";"";
"R4";"10K";"RESISTOR0603-RES";"0603-RES";"Resistor";"";
"R5";"10K";"RESISTOR0603-RES";"0603-RES";"Resistor";"";
"RESET";"";"TAC_SWITCHPTH";"TACTILE-PTH";"Momentary Switch";"";
"TRST";"";"SWITCH-SPDTPTH";"SWITCH-SPDT";"SPDT Switch";"";
"VAGND";"";"JP1E";"JP1";"JUMPER";"";
"VAREF";"";"JP1E";"JP1";"JUMPER";"";
"Y1";"8Mhz";"CRYSTALSMD";"HC49UP";"Various standard crystals. Proven footprints. Spark Fun Electronics SKU : COM-00534";"";
